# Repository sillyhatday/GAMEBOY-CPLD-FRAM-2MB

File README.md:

# GAMEBOY-MBC5-CPLD-2MB

>[!WARNING]
>Current circuit board revision does not include support for the MAX7000 or ATF150x CPLD without bodges.

## Introduction:

This is my take of a CPLD based flash cart for the Gameboy.

The whole project is based from Alex's project from years back. Without that project, I would never have picked this up and spend my time figuring out how to work with CPLDs. I am not a programmer and do not claim to be. Picking up Alex's code I can see how things work with my previous knowledge of how carts operate.

The newest update has been done with the help of AI. I just wanted to get this thing done so it is off my active project list. Even though AI has helped, I have learned a little bit more about how CPLDs work because of it. In the future I'd like to use the knowledge to do another project.

Some reasons to build this project are:

	+ No need for sourcing a donor cartridge
	+ Multi MBC compatibility
	+ Cheaper to build vs a donor cart (initially not, more made, more saved)

>[!IMPORTANT]
> This project is designed with MBC5 functionality as the main priority. Compatibility with MBC1 is added on top, therefore, compatibility is not guaranteed. Super Mario Land 2 & Zelda: Link's Awakening work here, where they have issues running on a normal MBC5 chip. However, Donkey Kong Land does not work. Maybe one day I can create an MBC1 CPLD mapper.

>[!NOTE]
>For updates, see towards the end of the readme

## 🟦 Project State:

### :green_circle: Done

	- Get a cartridge that works well enough
	- Make the Altera 3032A & 3064A both work
	- Fix SRAM problems with MAX7000 and edge case MAX3000
	- Fix this readme after half updating and rage quitting. Remove V2.0 PCB pics.
	- Write draft of instructions for programming Atmel chips

### :yellow_circle: In Progress

	- Do some power tests of carts I have built so far.

### :white_circle: To Do

	- Test flashing Atmel chips in circuit
	- Design some hardware to flash Atmel chips in circuit
	- Update PCB to include solder jumper for different CPLD families.
	- Some issues with SRAM in FlashGBX with Atmel 1502A. Check hardware over & adjust SVF export settings.
	- Move FRAM chip select glue logic into software.

## 🟨 Prerequisites

	* The full components parts list and cart PCB
	* (Optional) JTAG adaptor PCB
	* Altera USB Blaster or FT232 for JTAG (cheap clones work)
	* Windows PC with Quartus II Programmer, Quartus II Web Edition or OpenOCD
	* GBxCart and related software
 	* Modified Gameboy cart shell or (optional) 3D printed Game Gear cart adaptor
	* Equipment to solder tiny SMD components
	* Skills to solder tiny SMD components reliably

## 🔌 CPLD Information

>[!TIP]
>Information on chosing a CPLD <br>
>[ALTERA PROGRAMMING GUIDE](AlteraProgrammingGuide.md) <br>
>[ATMEL PROGRAMMING GUIDE](AtmelProgrammingGuide.md) <br>
>[CPLD POWER USAGE](CartPowerUse.md) <br>

Prices vary, these are typical.

| Model | Cost x1 | Vendor |
| ----- | ------- | ------ |
| 3032A: | €1.16 | Aliexpress |
| 3064A: | €1.60 | Aliexpress |
| 7032S: | €1.85 | Aliexpress |
| 1504A: | €1.97 | Mouser |

Depending on the model, the AP2127K-3.3TRG1 may not be needed.

| Model | AP2127K | Jumper |
| ----- | ------- | ------ |
| 3032A | YES | NO |
| 3064A | YES | NO |
| 7032S | NO | YES |
| 1502A | NO | YES |

## 🟦 Parts List

### Cartridge x1

>[!IMPORTANT]
>When ordering cartridge PCBs, make sure to choose 0.8mm thickness and gold plating. <br>
>Altera MAX3000 & MAX7000 CPLDs are obselete and only found on Aliexpress. I suggest the 3032A. (MAX7000 is a relic at this point). <br>
>If ordering MAX7000, get the S version, otherwise throw your money in a fire. Eg, EPM7032S <br>
>Atmel ATF150x parts can be bought new from reputable sellers. However they are trickier to program for the average person. <br>
>Order FRAM from Aliexpress & eBay at your own risk, they are known to be ***extremely*** unreliable. <br>

| Part No. | Package | Qty |
| -------- | ------- | --- |
| 29F016 | TSOP48 | 1 |
| FM1808 | SOIC28 | 1 |
| CPLD* | TQFP44 | 1 |
| 74LVC1G332 | TSOP6 | 1 |
| AP2127K-3.3TRG1** | SOT23-5 | 1 |
| Cap 100nF | 0603 | 4 |
| Cap 1uF | 0603 | 2 |
| Res 10K | 0603 | 1 |

**EPM3064A, EPM3032A, EPM7064S, EPM7032S, ATF1504A or ATF1502A*
***See CPLD info*

### JTAG Adaptor

| Part No. | Qty |
| -------- | --- |
| DS Lite Cart Conn | 1 |
| USB C USB4125 | 1 |
| Pin Headers | 2x5-P2.54mm |
| GG Adaptor or Shell | 1 |
| USB Blaster | 1 |

>[!TIP]
>Link to [Game Gear Adaptor](https://www.thingiverse.com/thing:5830799)

## Build Photos

**Different CPLD** <br>

**Original Prototype** <br>

## Update June 2026

I've picked this back up again when I found a PCB laying about. I had to wonder if AI was good enough now to help improve things. It is fortunately.

The previous update I was naive to think programming in C++ was anything like Verilog. I mean it is, but the device being programmed works so differently to other CPU based systems.

The issue that has been plaguing the 7032S & 1504A, is the save RAM functionality. Games would not save, or correctly use the cartridge as work RAM. This was on the Gameboy and cart readers. I tested this over a few carts and the first one kinda worked. It was flaky but saving, yet only on the GB and not the cart reader. There worst problem is that this problem crept into some of the 3032A and 3064A carts also.

This code refactor seems to have fixed all these problems, not only the MAX3000 but the MAX7000 also. As of now, the ATF1504 is untested. I am hopeful that it will work also. Programming those is more complex and I've since forgotten how to do it.

The smaller EPM3032A, EPM7032S & ATF1502 with 32 macro cells are now more than big enough to fit the program, no longer is it so tight. This is thanks to removing the 128KB RAM functionality, reducing the amount of registers required to address that has gained a lot of space. Additional code can be added for more functionality such as moving the FRAM gate logic into the CPLD and making it user programmable with a solder bridge on the PCB.

This is all very nice as the smaller chips tend to use less power than the larger counterparts, even though they use the same quantity of macro cells. I'll add more detailed information on the changes in its own readme.

When the Atmel part is confirmed working, I'll update the rest of the readme to walk though programming those. Ideally the PCB could use a revision to add the FRAM mode jumper and a jumper to bypass the 3.3v regulator when using the MAX7000 and ATF15xx chips. Again, I'll get to that when testing is complete.

## Firmware Versions

| Version | Status | Notes |
| ------- | ------ | ----- |
| V1.0.0  | Initial | Original code from Alex's blog |
| V1.0.1  | Fix | Removed internal FRAM chip select logic to lower cartridge power consumption 1 to 3% |
| V2.0.0  | Fix | Changed project compiler settings to lower cartridge power consumption 36 to 41% |
| V3.0.0  | Current | AI helper to teach me and structure code better. Use of macro cells more efficient. Logic split into smaller sections. More reliable, cleaner code, better output waveforms (I need to confirm that). |

## 🩷 Links

🔧 Driver Install: https://www.terasic.com.tw/wiki/Intel_USB_Blaster_Driver_Installation_Instructions <br>
⬇️ Driver Download: https://github.com/sudhamshu091/USB-Blaster-Driver-for-DE10-lite <br>
🖨️ Game gear Adaptor: https://www.thingiverse.com/thing:5830799 <br>
⏬ Alt Link Quartus: https://archive.org/details/quartus-iiprogrammer-and-signal-tap-ii-13.1.0.162.7z <br>
🛍️ Inside Gadgets Shop: https://shop.insidegadgets.com <br>
📎 Inside Gadgets GitHub: https://github.com/insidegadgets <br>
📷 Inside Gadgets Insta: https://www.instagram.com/inside.gadgets <br>
🖇️ Bytendo Mods GitHub: https://github.com/bytendomods <br>
🐭 Bucket Mouse: https://github.com/Bucket-Mouse <br>
🛒 Natalie Shop: https://nataliethenerd.com/ <br>
🤓 Natalie GitHub: https://github.com/natalie-lang/natalie <br>

Thanks to Xukkorz, Drew, Jamo, Alex, Deceptive Thinker, Natalie the Nerd & anyone else who I may have forgotten.

## License

This work is licensed under a Creative Commons Attribution-ShareAlike 4.0 International License. You are able to copy and redistribute the material in any medium or format, as well as remix, transform, or build upon the material for any purpose (even commercial) - but you must give appropriate credit, provide a link to the license, and indicate if any changes were made.

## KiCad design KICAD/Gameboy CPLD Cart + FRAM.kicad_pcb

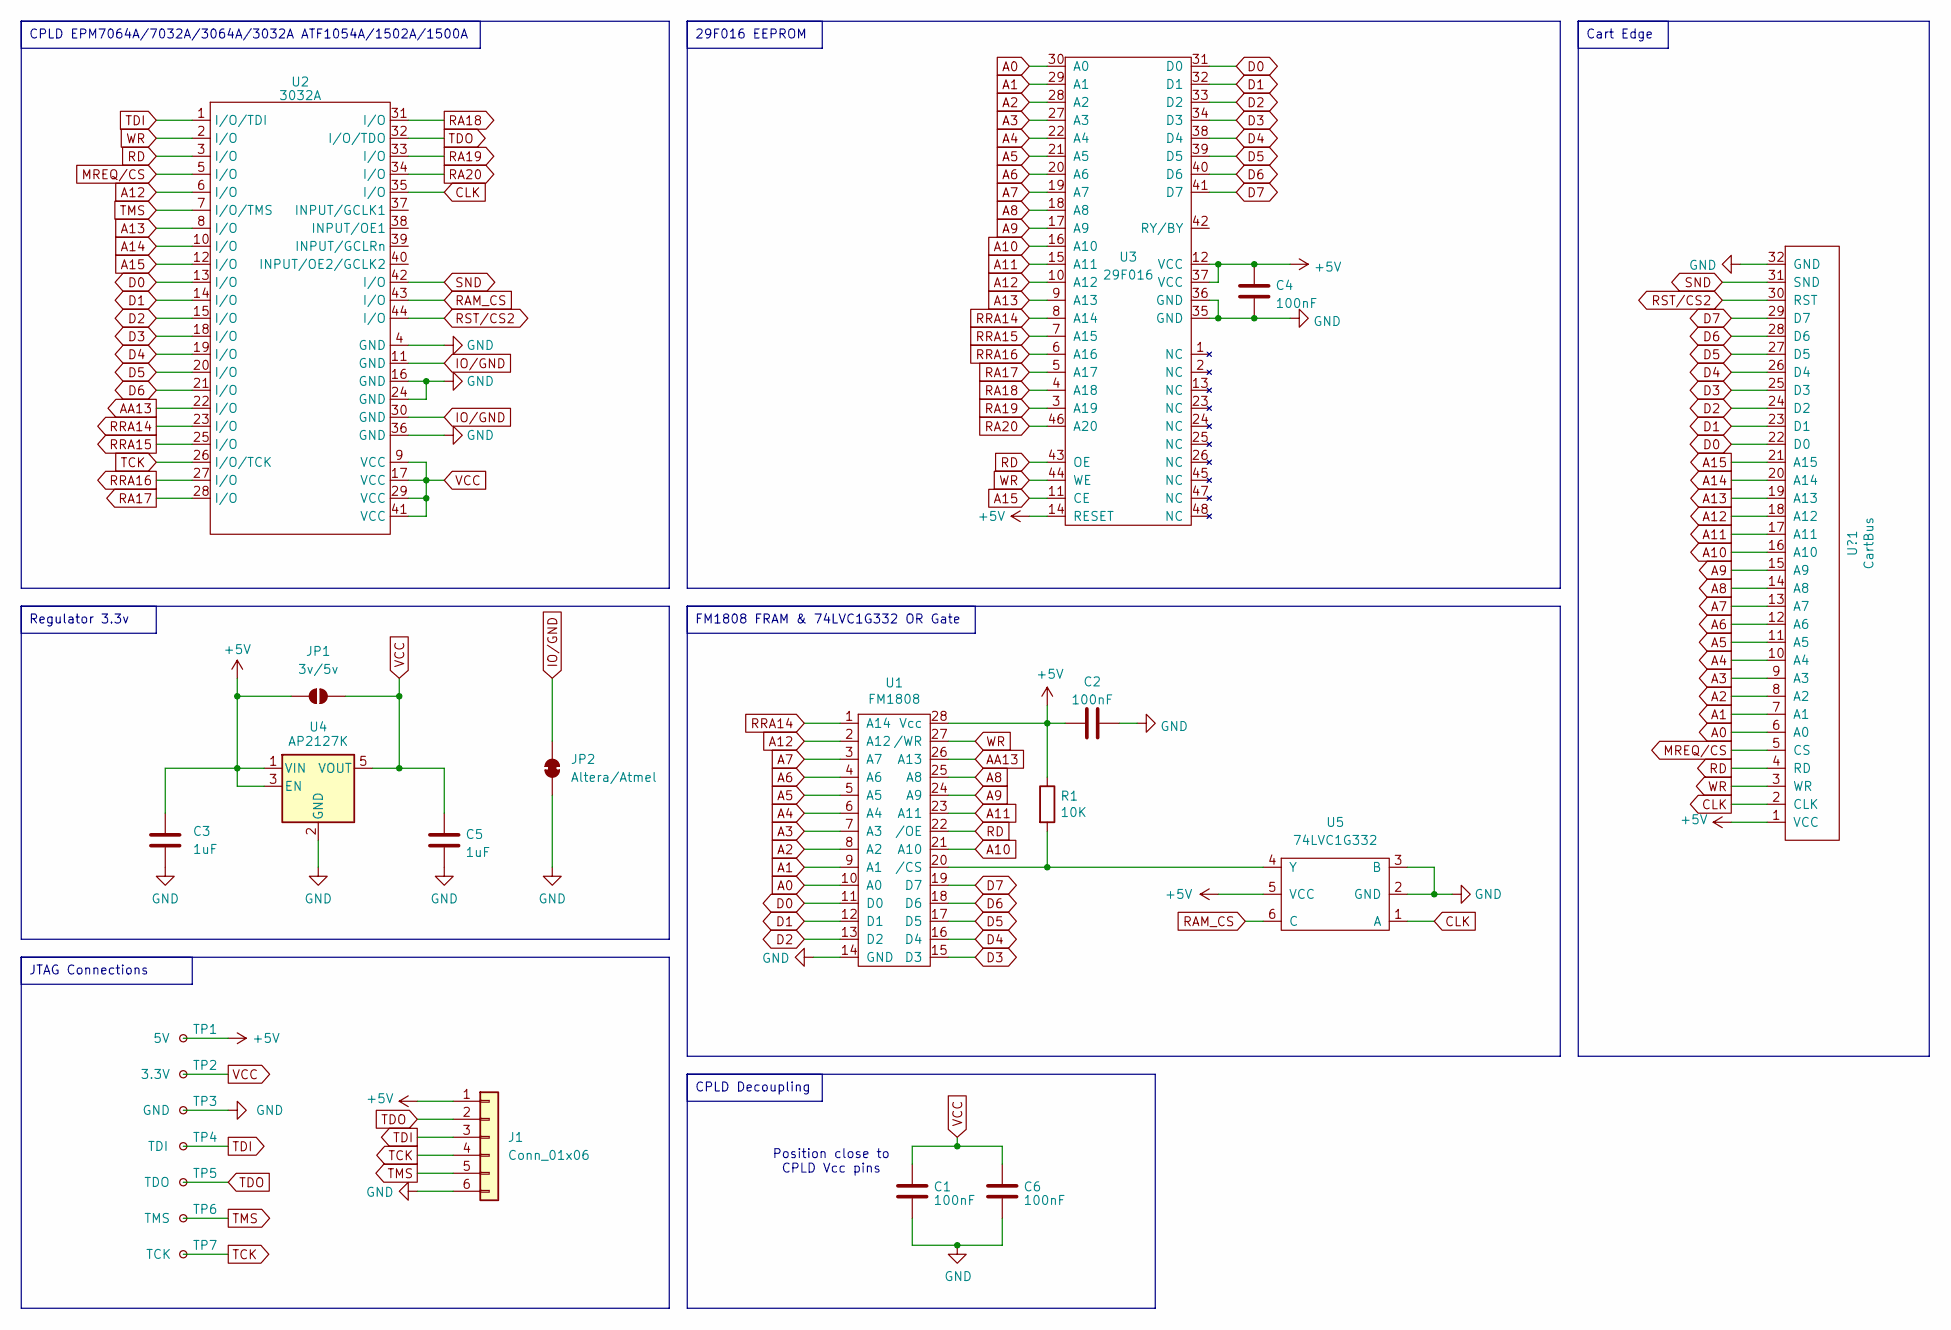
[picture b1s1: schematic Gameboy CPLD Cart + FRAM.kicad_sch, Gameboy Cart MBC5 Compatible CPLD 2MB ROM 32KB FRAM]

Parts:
C1, C2, C4, C6: 100nF; C_0603_1608Metric_Pad1.08x0.95mm_HandSolder
C3, C5: 1uF; C_0603_1608Metric_Pad1.08x0.95mm_HandSolder
J1: Conn_01x06; JTAG Cart Edge Connector
JP1: 3v/5v; SolderJumper-2_P1.3mm_Open_RoundedPad1.0x1.5mm
JP2: Altera/Atmel; SolderJumper-2_P1.3mm_Bridged_RoundedPad1.0x1.5mm
R1: 10K; R_0603_1608Metric_Pad0.98x0.95mm_HandSolder
TP1: 5V; TestPoint_Pad_D1.0mm
TP2: 3.3V; TestPoint_Pad_D1.0mm
TP3: GND; TestPoint_Pad_D1.0mm
TP4: TDI; TestPoint_Pad_D1.0mm
TP5: TDO; TestPoint_Pad_D1.0mm
TP6: TMS; TestPoint_Pad_D1.0mm
TP7: TCK; TestPoint_Pad_D1.0mm
U1: FM1808; SOIC-28W_7.5x17.9mm_P1.27mm
U2: 3032A; TQFP-44_10x10mm_P0.8mm
U3: 29F016; TSOP-I-48_18.4x12mm_P0.5mm
U4: AP2127K; SOT-23-5
U5: 74LVC1G332; TSOP-6_1.65x3.05mm_P0.95mm
U?1: CartBus; GameBoy_GamePak_DMG-09_P1.50mm_Edge

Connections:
+5V: C2.1, C3.1, C4.1, J1.1, JP1.1 (A), R1.1, TP1.1, U1.28 (Vcc), U3.12 (VCC), U3.14 (RESET), U3.37 (VCC~), U4.1 (VIN), U4.3 (EN), U5.5 (VCC), U?1.1 (VCC)
A0: U1.10 (A0), U3.30 (A0~), U?1.6 (A0)
A1: U1.9 (A1), U3.29 (A1), U?1.7 (A1)
A2: U1.8 (A2), U3.28 (A2), U?1.8 (A2)
A3: U1.7 (A3), U3.27 (A3), U?1.9 (A3)
A4: U1.6 (A4), U3.22 (A4), U?1.10 (A4)
A5: U1.5 (A5), U3.21 (A5), U?1.11 (A5)
A6: U1.4 (A6), U3.20 (A6), U?1.12 (A6)
A7: U1.3 (A7), U3.19 (A7), U?1.13 (A7)
A8: U1.25 (A8), U3.18 (A8), U?1.14 (A8)
A9: U1.24 (A9), U3.17 (A9), U?1.15 (A9)
A10: U1.21 (A10), U3.16 (A10), U?1.16 (A10)
A11: U1.23 (A11), U3.15 (A11), U?1.17 (A11)
A12: U1.2 (A12), U2.6 (I/O), U3.10 (A12), U?1.18 (A12)
A13: U2.8 (I/O), U3.9 (A13), U?1.19 (A13)
A14: U2.10 (I/O), U?1.20 (A14)
A15: U2.12 (I/O), U3.11 (CE), U?1.21 (A15)
AA13: U1.26 (A13), U2.22 (I/O)
CLK: U2.35 (I/O), U5.1 (A), U?1.2 (CLK~)
D0: U1.11 (D0), U2.13 (I/O), U3.31 (D0), U?1.22 (D0)
D1: U1.12 (D1), U2.14 (I/O), U3.32 (D1), U?1.23 (D1)
D2: U1.13 (D2), U2.15 (I/O), U3.33 (D2), U?1.24 (D2)
D3: U1.15 (D3), U2.18 (I/O), U3.34 (D3), U?1.25 (D3)
D4: U1.16 (D4), U2.19 (I/O), U3.38 (D4), U?1.26 (D4)
D5: U1.17 (D5), U2.20 (I/O), U3.39 (D5), U?1.27 (D5)
D6: U1.18 (D6), U2.21 (I/O), U3.40 (D6), U?1.28 (D6)
D7: U1.19 (D7), U3.41 (D7), U?1.29 (D7)
GND: C1.1, C2.2, C3.2, C4.2, C5.2, C6.1, J1.6, JP2.1 (A), TP3.1, U1.14 (GND), U2.4 (GND), U2.16 (GND), U2.24 (GND), U2.36 (GND), U3.35 (GND), U3.36 (GND), U4.2 (GND), U5.2 (GND), U5.3 (B), U?1.32 (GND)
IO/GND: JP2.2 (B), U2.11 (GND), U2.30 (GND)
MREQ/CS: U2.5 (I/O), U?1.5 (CS)
unnamed: R1.2, U1.20 (/CS), U5.4 (Y)
RA17: U2.28 (I/O), U3.5 (A17)
RA18: U2.31 (I/O), U3.4 (A18)
RA19: U2.33 (I/O), U3.3 (A19)
RA20: U2.34 (I/O), U3.46 (A20)
RAM_CS: U2.43 (I/O), U5.6 (C)
RD: U1.22 (/OE), U2.3 (I/O), U3.43 (OE~), U?1.4 (RD)
RRA14: U1.1 (A14), U2.23 (I/O), U3.8 (A14)
RRA15: U2.25 (I/O), U3.7 (A15)
RRA16: U2.27 (I/O), U3.6 (A16)
RST/CS2: U2.44 (I/O), U?1.30 (RST)
SND: U2.42 (I/O), U?1.31 (SND)
TCK: J1.4, TP7.1, U2.26 (I/O/TCK)
TDI: J1.3, TP4.1, U2.1 (I/O/TDI)
TDO: J1.2, TP5.1, U2.32 (I/O/TDO)
TMS: J1.5, TP6.1, U2.7 (I/O/TMS)
VCC: C1.2, C5.1, C6.2, JP1.2 (B), TP2.1, U2.9 (VCC), U2.17 (VCC), U2.29 (VCC), U2.41 (VCC), U4.5 (VOUT)
WR: U1.27 (/WR), U2.2 (I/O), U3.44 (WE), U?1.3 (WR)

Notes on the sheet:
CPLD Decoupling
Cart Edge
JTAG Connections
FM1808 FRAM & 74LVC1G332 OR Gate
CPLD EPM7064A/7032A/3064A/3032A ATF1054A/1502A/1500A
29F016 EEPROM
Regulator 3.3v
Position close to CPLD Vcc pins

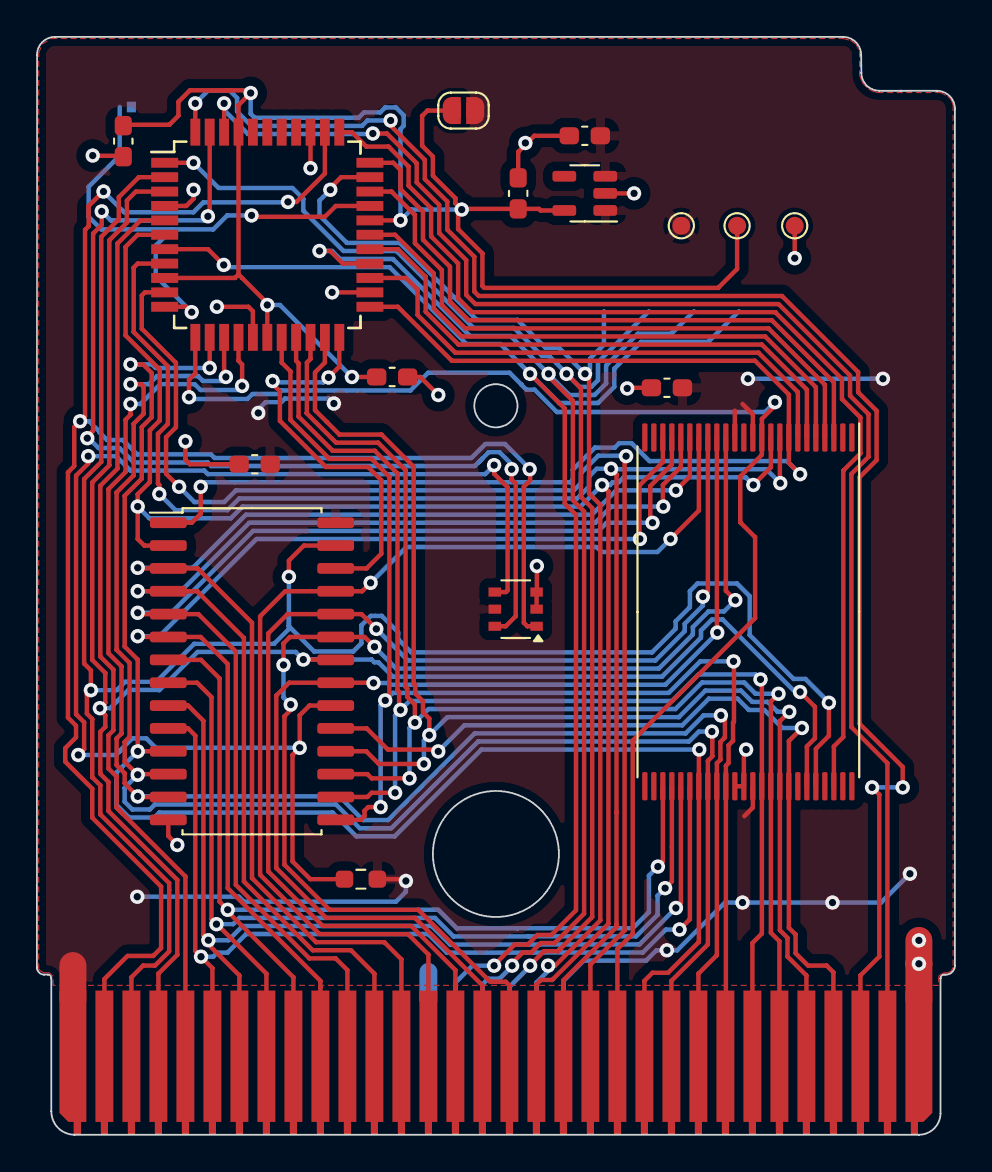
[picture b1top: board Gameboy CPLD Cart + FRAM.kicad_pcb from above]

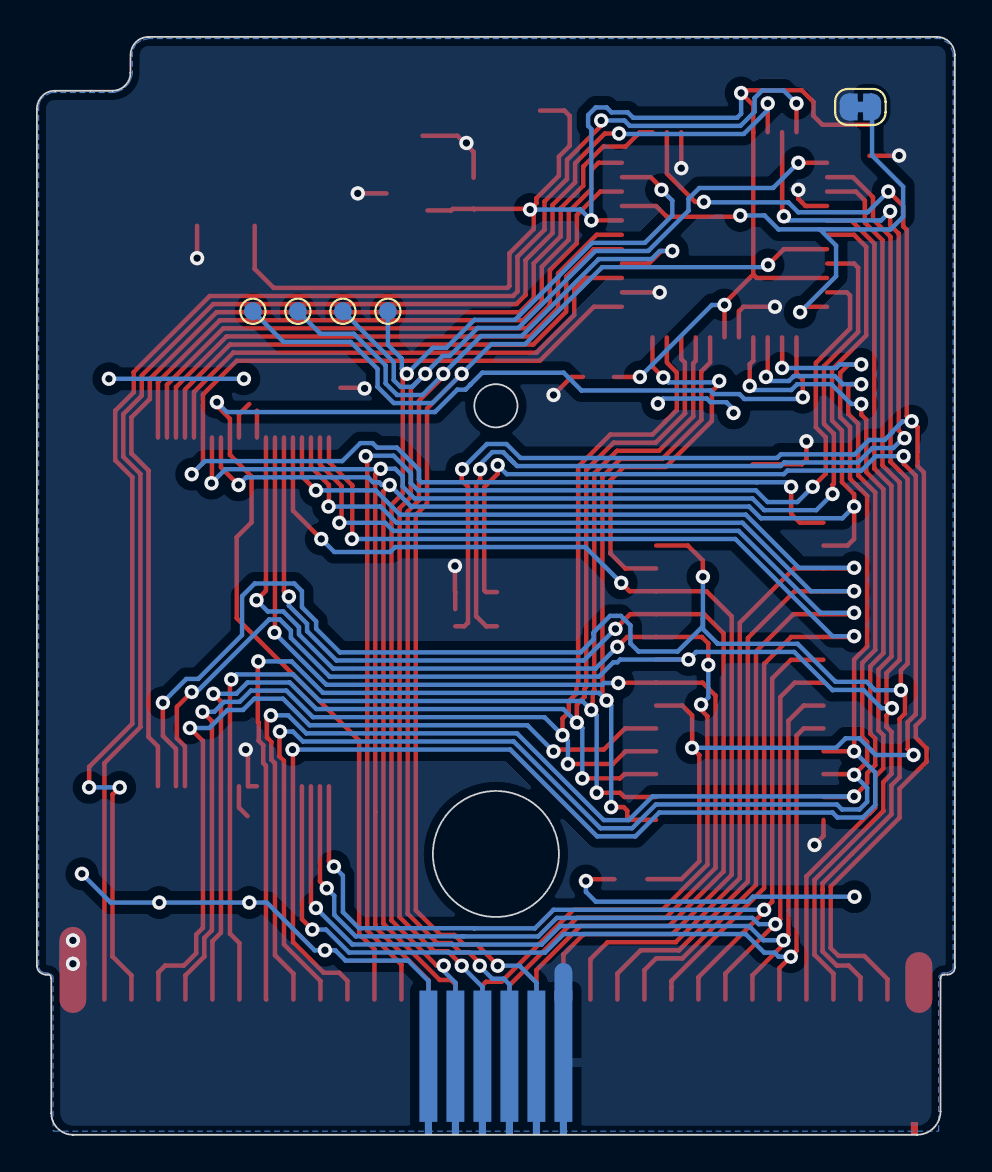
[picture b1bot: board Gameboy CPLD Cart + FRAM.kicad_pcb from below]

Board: 2 copper layers, 51.0 x 61.0 mm, 23 parts (6 on the bottom side), 48 nets.

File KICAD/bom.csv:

Designator,Footprint,Quantity,Value,LCSC Part #
"C1, C2, C4, C6",0603,4,100nF,
"C3, C5",0603,2,1uF,
J1,JTAG Cart Edge Connector,1,Conn_01x06,
R1,0603,1,10K,
TP1,TestPoint_Pad_D1.0mm,1,5V,
TP2,TestPoint_Pad_D1.0mm,1,VCC,
TP3,TestPoint_Pad_D1.0mm,1,GND,
TP4,TestPoint_Pad_D1.0mm,1,TDI,
TP5,TestPoint_Pad_D1.0mm,1,TDO,
TP6,TestPoint_Pad_D1.0mm,1,TMS,
TP7,TestPoint_Pad_D1.0mm,1,TCK,
U1,SOIC-28W_7.5x17.9mm_P1.27mm,1,FM1808,
U2,TQFP-44_10x10mm_P0.8mm,1,3032A,
U3,TSOP-I-48_18.4x12mm_P0.5mm,1,29F016,
U4,SOT-23-5,1,AP2127K,
U5,TSOP-6_1.65x3.05mm_P0.95mm,1,74LVC1G332,
U?1,GameBoy_GamePak_DMG-09_P1.50mm_Edge,1,CartBus,

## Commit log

2025-05-28 Delete CPLD Prog Files/mbc5_2mb_v1_3032a.7z
    preparing for new firmware
2025-05-28 Delete CPLD Prog Files/mbc5_2mb_v1_3064a.7z
    Preparing for new firmware
2025-05-28 Create Altera EPM3064A
    Adding new firmware
2025-05-28 Update readme.md
    Adding new firmware
2025-05-28 Create Altera EPM3032A
2025-05-28 Delete CPLD Prog Files/Altera EPM3032A
    error
2025-05-28 Delete CPLD Prog Files/Altera EPM3064A
    error
2025-05-28 Create readme.md
    Updating firmware
2025-05-28 3032A firmware update
    all firmware versions uploaded
2025-05-28 New firmware
    uploaded all firmware versions
2025-05-28 Update README.md
    Added section on firmware versions
2025-05-28 Update README.md
    typos fixed
2025-05-28 Update README.md
    reworded firmware section and removed alex blog reference at the top
2025-05-28 Create LICENSE
    Added license
2025-05-28 Create License.md
    changed license
2025-05-29 Delete Software directory
    Removed proprietary programming software
2025-05-29 Delete GerberFiles directory
    Removed V1 gerbers to tidy up
2025-05-29 Update PowerUse.md
    Large formatting update and added placeholders for v2.0 firmware
2025-05-29 Create AlteraProgramming.md
    Programming guide added
2025-05-29 Update README.md
    Removed programming guide from main readme
2025-05-29 Create AtmelProgrammingGuide.md
    Place holder programming guide
2025-05-29 Update PowerUse.md
    Updated MAX7000 series part numbers to correct ones
2025-05-29 Update PowerUse.md
    Place holders added for Atmel devices
2025-05-29 Update PowerUse.md
    Added v2 3064a power figures
2025-05-29 Update PowerUse.md
    updated average table
2025-05-30 Update PowerUse.md
    Added 3032A power figures
2025-05-30 Update PowerUse.md
    Typo fix
2025-06-01 Update README.md
    Updated readme for V2 PCB
2025-06-06 Update PowerUse.md
    added some data for 7032S and 1502A
2025-06-09 Update README.md
    added compatibility issue note
2025-12-08 Update README.md
    Update
2026-06-22 Update README.md
    NEW SOFTWARE! FRAM problems FIXED
2026-06-22 Create CodeNotes&Summary.md
    Added document on changes to code and a bit of info on CPLDs in general
2026-06-22 New R3 firmware
2026-06-22 Add files via upload
    v3 firmware POF
2026-06-22 Update [AI + SillyHatDay] GB MBC5-1 Hybrid - R3 (2MB ROM, 32KB RAM).v
    Added comments
2026-06-22 Update [AI + SillyHatDay] GB MBC5-1 Hybrid - R3 (2MB ROM, 32KB RAM).v
    Few extra comments
2026-06-22 Update README.md
    Added progress log
2026-06-23 Update [AI + SillyHatDay] GB MBC5-1 Hybrid - R3 (2MB ROM, 32KB RAM).v
    updated comments
2026-06-23 Update AtmelProgrammingGuide.md
    First Atmel programming draft
2026-06-23 Update README.md
    Huge update
2026-06-23 Update README.md
    New photos, typos
2026-06-23 Rename AlteraProgramming.md to AlteraProgrammingGuide.md
    renamed
2026-06-23 Update README.md
    Links to guides
2026-06-23 Update AlteraProgrammingGuide.md
    huge update
2026-06-23 Update README.md
    Important warning information
2026-06-23 Update README.md
    modded prerequisitiieseiseisi
2026-06-23 Update README.md
    typo
2026-06-23 Update README.md
    warning added
2026-06-23 Update README.md
    updated to do
2026-06-24 Rename PowerUse.md to ARCHIVE/PowerUseOld.md
    archived old power use stats
2026-06-24 Create CartPowerUse.md
    New power charts, mid point save
2026-06-24 Update README.md
    Pricing added
2026-06-24 Update README.md
    Added info on vreg requirements
2026-06-24 Update README.md
    linked power usage doc
2026-06-25 Create meow moew nya?
